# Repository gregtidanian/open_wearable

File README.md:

A wearable device that is designed for the purpose of testing Daedalus.

The device is designed using the following sub-groups.

**Microcontroller**

The microcontroller is part of the Fanstell BT40 module, containing the Nordic nRF5340 microprocessor.

**Motion Sensor**

The motion sensor is the MPU-6050, which is a 6-axis gyroscope and accelerometer.

**Flash Memory**

The Serial NOR Flash Memory chip is the MX25R6435FM2IL0 component.

**Programming**

Programming and flashing the device is done via the SWD port, designed to mate with a TC2030-NL connector interface.

**RGB LEDs**

The design includes two WS2812 RGB LEDs.

**3.3V Output LDO**

The 3.3V output circuit includes the TPS62740DSSR low-dropout regulator.

**Charging**

The charging circuit includes the MCP73831-2-MC charging chip.

**USB-C**

The USB-C circuit includes the 632723300011 USB-C port.

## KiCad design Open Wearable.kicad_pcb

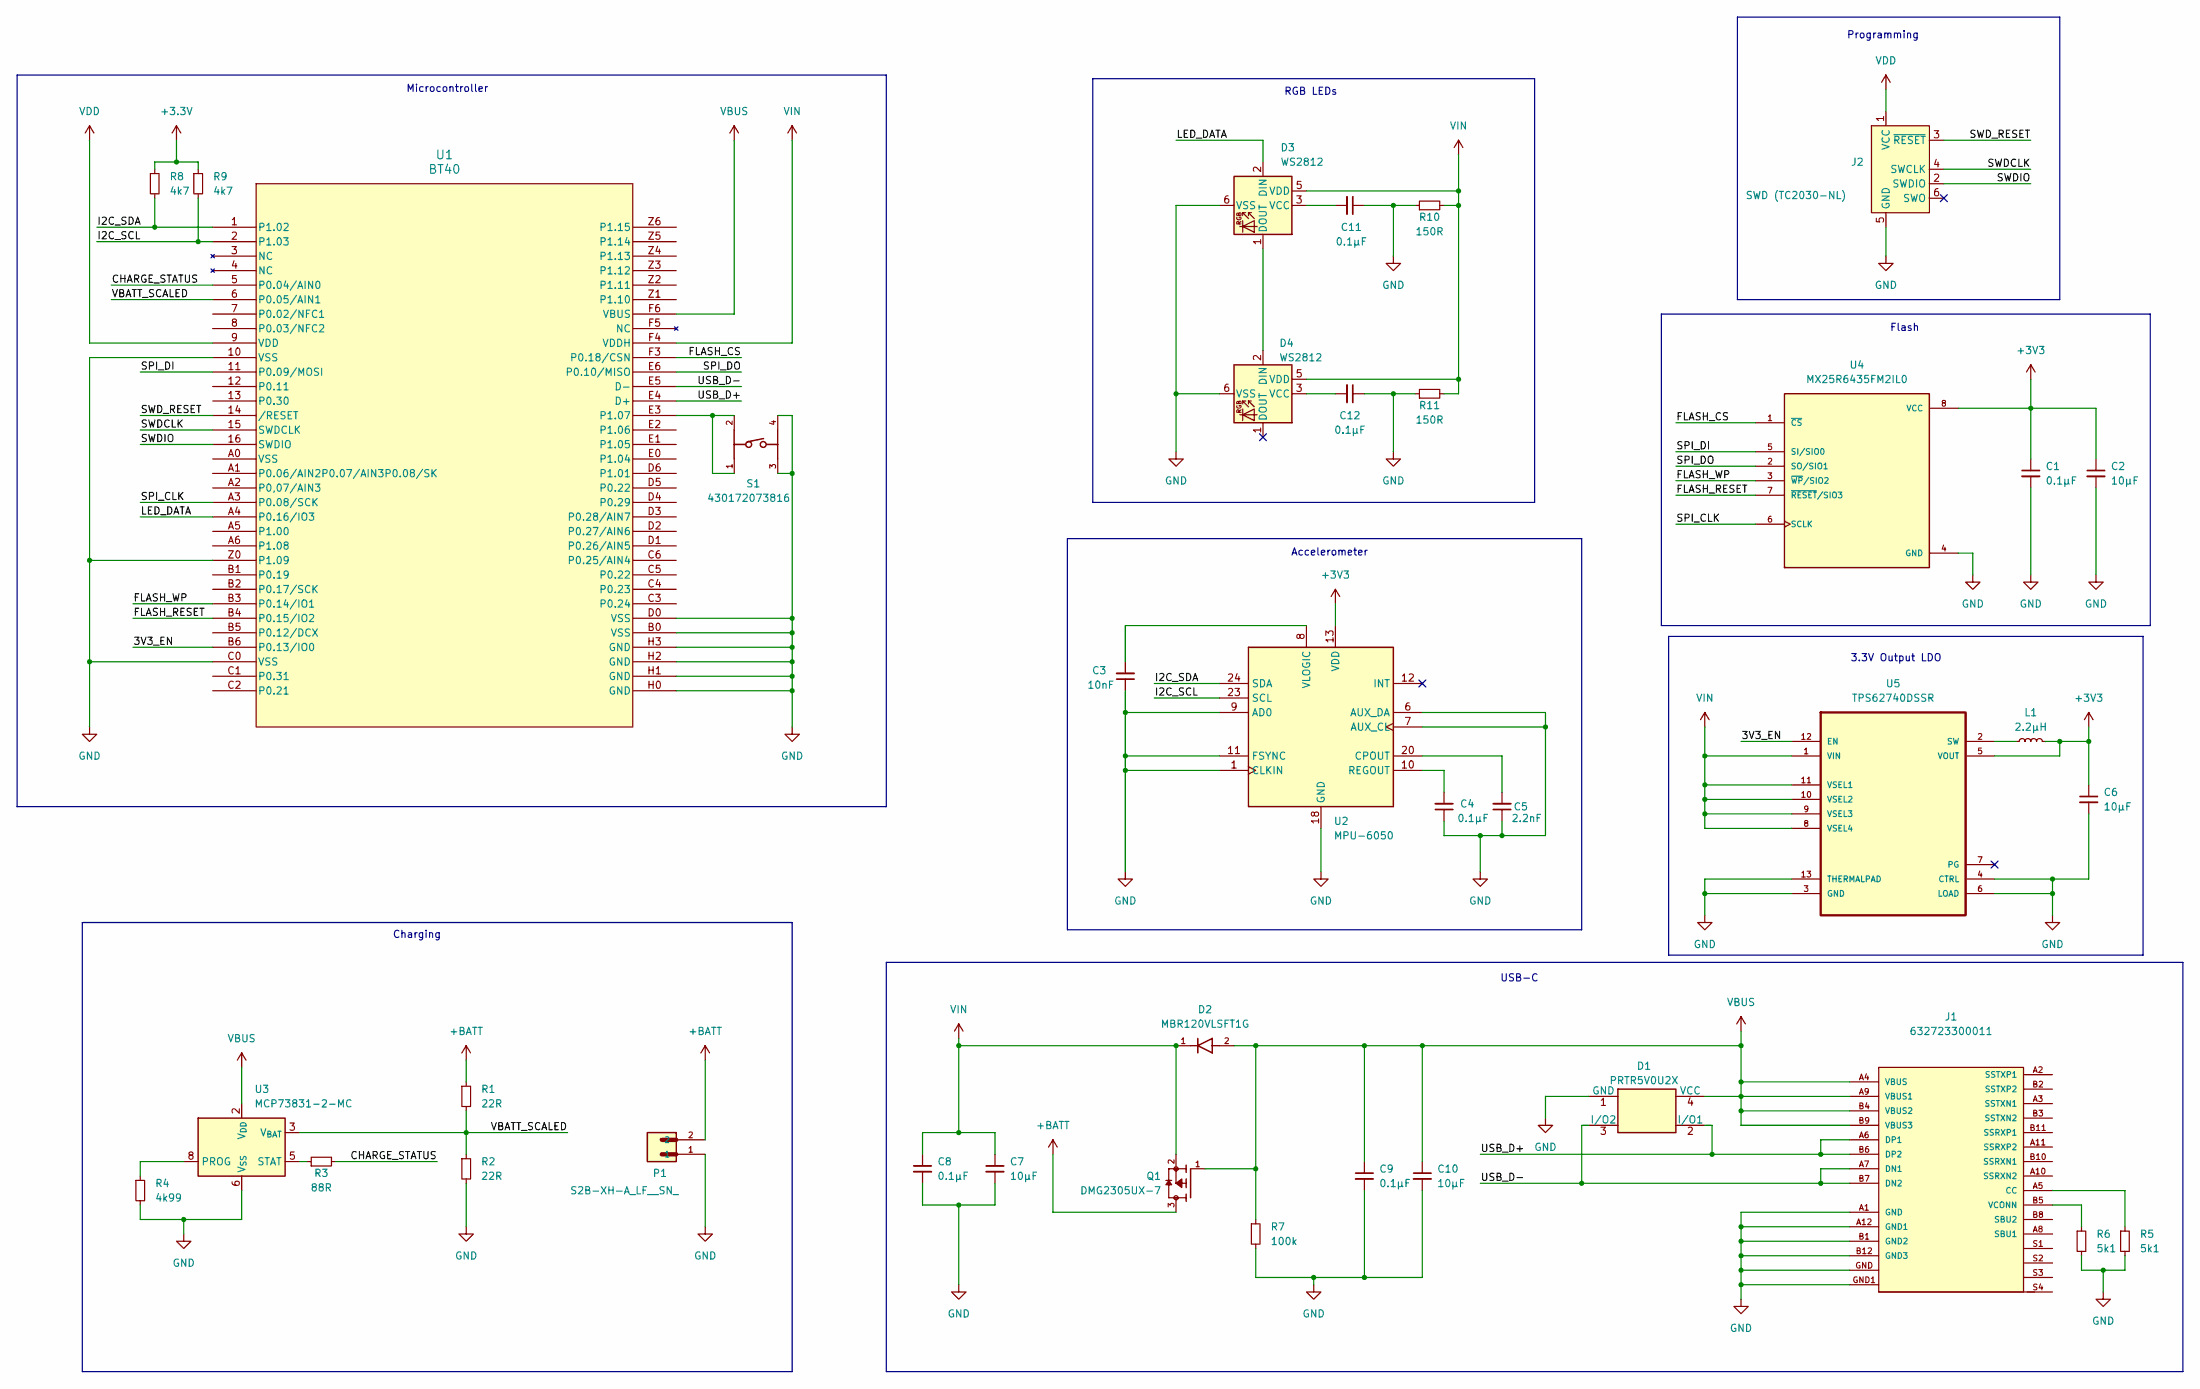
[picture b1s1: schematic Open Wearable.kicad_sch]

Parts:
C1, C4, C8, C9, C11, C12: 0.1µF; C_0603_1608Metric
C2, C6, C7, C10: 10µF; C_0603_1608Metric
C3: 10nF; C_0603_1608Metric
C5: 2.2nF; C_0603_1608Metric
D1: PRTR5V0U2X; SOT-143
D2: MBR120VLSFT1G; DIOM3616X98N; PARTREV 5/10/2013
D3, D4: WS2812; LED_WS2812_PLCC6_5.0x5.0mm_P1.6mm
J1: 632723300011; PART-NUMBER 632723300011
J2: SWD (TC2030-NL); Tag-Connect_TC2030-IDC-NL_2x03_P1.27mm_Vertical
L1: 2.2µH; L_Coilcraft_LPS3010
P1: S2B-XH-A_LF__SN_; JST_S2B-XH-A_LF__SN_
Q1: DMG2305UX-7; SOT91P240X110-3N_DMG2305UX-7; PARTREV 09/2018
R1, R2: 22R; R_0603_1608Metric
R3: 88R; R_0603_1608Metric
R4: 4k99; R_0603_1608Metric
R5, R6: 5k1; R_0603_1608Metric
R7: 100k; R_0603_1608Metric
R8, R9: 4k7; R_0603_1608Metric
R10, R11: 150R; R_0603_1608Metric
S1: 430172073816; PART-NUMBER 430172073816
U1: BT40; BT40E_FAN_FNL
U2: MPU-6050; InvenSense_QFN-24_4x4mm_P0.5mm
U3: MCP73831-2-MC; DFN-8-1EP_3x2mm_P0.5mm_EP1.7x1.4mm
U4: MX25R6435FM2IL0; SOIC127P790X216-8N; PARTREV 1.6
U5: TPS62740DSSR; SON50P300X200X80-13N

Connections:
+3.3V: R8.1, R9.1
+3V3: C1.1, C2.1, C6.1, L1.2, U2.13 (VDD), U4.8 (VCC), U5.5 (VOUT)
+BATT: P1.2, Q1.3, R1.1
/3V3_EN: U1.B6 (P0.13/IO0), U5.12 (EN)
/CHARGE_STATUS: R3.2, U1.5 (P0.04/AIN0)
/FLASH_CS: U1.F3 (P0.18/CSN), U4.1 (~CS)
/FLASH_RESET: U1.B4 (P0.15/IO2), U4.7 (~RESET/SIO3)
/FLASH_WP: U1.B3 (P0.14/IO1), U4.3 (~WP/SIO2)
/I2C_SCL: R9.2, U1.2 (P1.03), U2.23 (SCL)
/I2C_SDA: R8.2, U1.1 (P1.02), U2.24 (SDA)
/LED_DATA: D3.2 (DIN), U1.A4 (P0.16/IO3)
/SPI_CLK: U1.A3 (P0.08/SCK), U4.6 (SCLK)
/SPI_DI: U1.11 (P0.09/MOSI), U4.5 (SI/SIO0)
/SPI_DO: U1.E6 (P0.10/MISO), U4.2 (SO/SIO1)
/SWDCLK: J2.4 (SWCLK), U1.15 (SWDCLK)
/SWDIO: J2.2 (SWDIO), U1.16 (SWDIO)
/SWD_RESET: J2.3 (~RESET), U1.14 (/RESET)
/USB_D+: D1.2 (I/O1), J1.A6 (DP1), J1.B6 (DP2), U1.E4 (D+)
/USB_D-: D1.3 (I/O2), J1.A7 (DN1), J1.B7 (DN2), U1.E5 (D-)
/VBATT_SCALED: R1.2, R2.1, U1.6 (P0.05/AIN1), U3.3 (V_{BAT}), U3.4 (V_{BAT})
GND: C1.2, C2.2, C3.1, C4.1, C5.1, C6.2, C7.2, C8.2, C9.2, C10.2, C11.1, C12.1, D1.1 (GND), D3.6 (VSS), D4.6 (VSS), J1.A1 (GND), J1.A12 (GND1), J1.B1 (GND2), J1.B12 (GND3), J1.GND, J1.GND1, J2.5 (GND), P1.1, R2.2, R4.2, R5.2, R6.2, R7.2, R10.1, R11.1, S1.3, S1.4, U1.10 (VSS), U1.B0 (VSS), U1.C0 (VSS), U1.D0 (VSS), U1.H0 (GND), U1.H1 (GND), U1.H2 (GND), U1.H3 (GND), U1.Z0 (P1.09), U2.1 (CLKIN), U2.6 (AUX_DA), U2.7 (AUX_CL), U2.9 (AD0), U2.11 (FSYNC), U2.18 (GND), U3.6 (V_{SS}), U4.4 (GND), U5.3 (GND), U5.4 (CTRL), U5.6 (LOAD), U5.13 (THERMALPAD)
unnamed: D3.1 (DOUT), D4.2 (DIN)
unnamed: C11.2, D3.3 (VCC)
unnamed: C12.2, D4.3 (VCC)
unnamed: J1.A5 (CC), R5.1
unnamed: J1.B5 (VCONN), R6.1
unnamed: S1.1, S1.2, U1.E3 (P1.07)
unnamed: C5.2, U2.20 (CPOUT)
unnamed: C4.2, U2.10 (REGOUT)
unnamed: C3.2, U2.8 (VLOGIC)
unnamed: R4.1, U3.8 (PROG)
unnamed: R3.1, U3.5 (STAT)
unnamed: L1.1, U5.2 (SW)
VBUS: C9.1, C10.1, D1.4 (VCC), D2.2, J1.A4 (VBUS), J1.A9 (VBUS1), J1.B4 (VBUS2), J1.B9 (VBUS3), Q1.1, R7.1, U1.F6 (VBUS), U3.1 (V_{DD}), U3.2 (V_{DD})
VDD: J2.1 (VCC), U1.9 (VDD)
VIN: C7.1, C8.1, D2.1, D3.5 (VDD), D4.5 (VDD), Q1.2, R10.2, R11.2, U1.F4 (VDDH), U5.1 (VIN), U5.8 (VSEL4), U5.9 (VSEL3), U5.10 (VSEL2), U5.11 (VSEL1)

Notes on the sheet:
RGB LEDs
Charging
Accelerometer
Programming
USB-C
Flash
Microcontroller
3.3V Output LDO

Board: 2 copper layers, 38 parts (0 on the bottom side), 36 nets, no tracks yet.
